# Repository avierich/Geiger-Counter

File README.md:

# Geiger-Counter

A simple geiger counter using a geiger-muller tube.

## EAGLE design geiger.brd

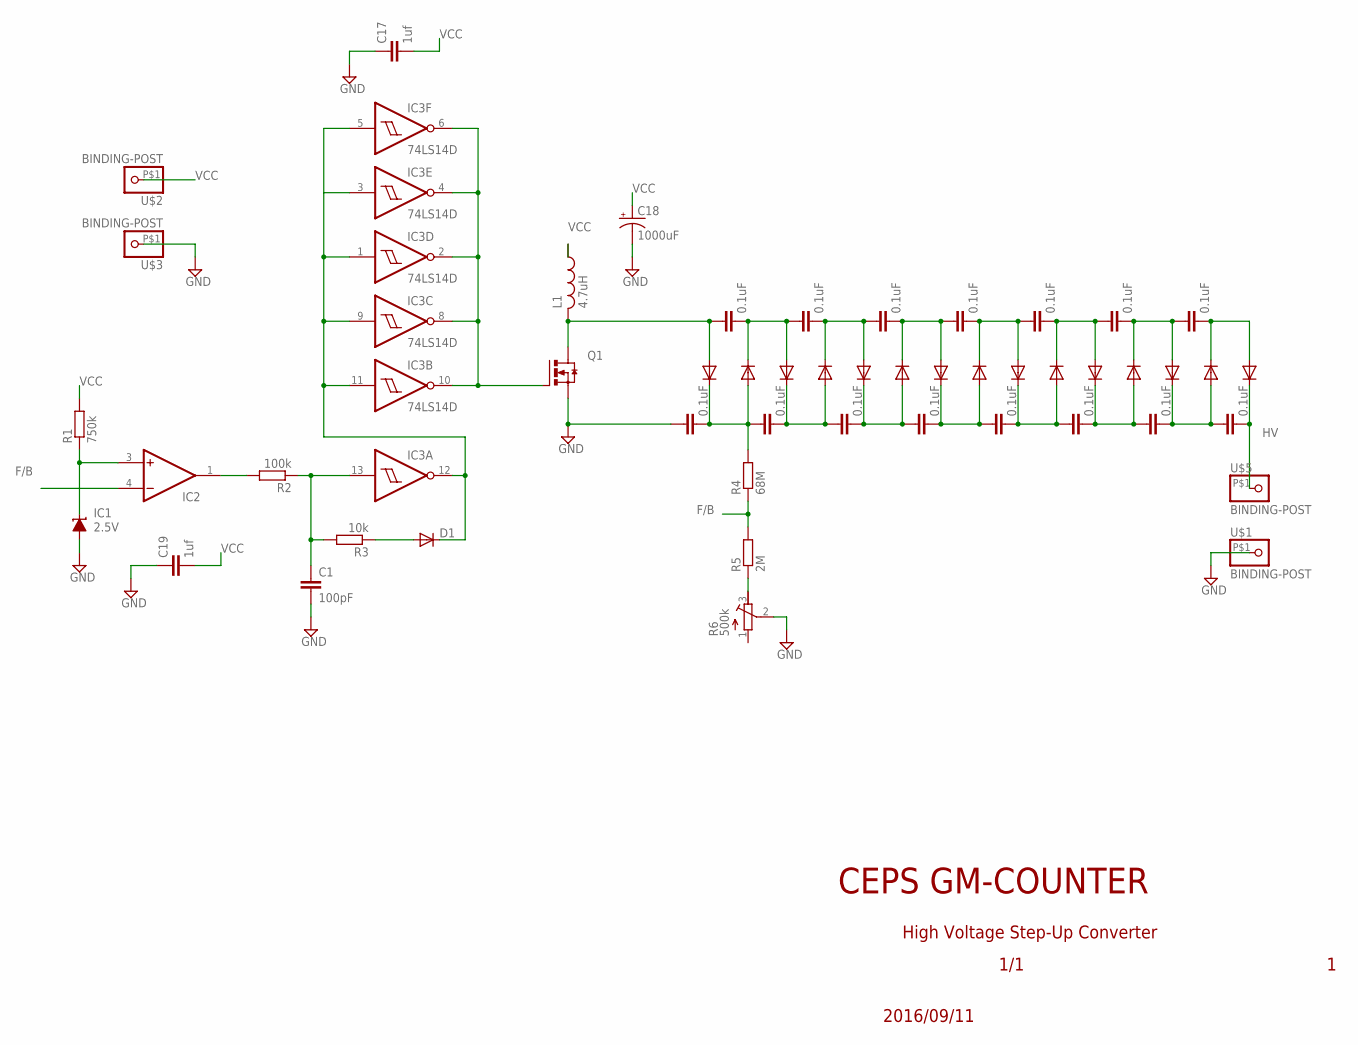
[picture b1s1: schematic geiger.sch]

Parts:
C1: 100pF; C0603
C2, C3, C4, C5, C6, C7, C8, C9, C10, C11, C12, C13, C14, C15, C16: 0.1uF; C0603
C17, C19: 1uf; C0603
C18: 1000uF; TT5D10
D1, D2, D3, D4, D5, D6, D7, D8, D9, D10, D11, D12, D13, D14, D15, D16: 1N4148DO35-7; DO35-7
IC1: 2.5V; DBZ_R-PDSO-G3
IC2: MAX4105EUK; SOT23-5L
IC3: 74LS14D; SO14
L1: 4.7uH; 6000-XXXX-RC
Q1: N-HEXFET-2D_SOT232-IRLL2705; SOT223
R1: 750k; R0603
R2: 100k; R0603
R3: 10k; R0603
R4: 68M; R0603
R5: 2M; R0603
R6: 500k; RTRIM4G/J
U$1, U$2, U$3, U$5: BINDING-POST

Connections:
+HV: C15.2, D15.C, D16.A
F/B: IC2.4 (-IN), R4.1, R5.2
GND: C1.2, C2.1, C17.1, C18.-, C19.1, IC1.2 (A), IC3.7 (GND), Q1.3 (S), R6.2 (S), U$1.P$1, U$3.P$1
HV: C16.2, D16.C, U$5.P$1
unnamed: IC1.1 (C), IC2.3 (+IN), R1.1
unnamed: D1.A, R3.1
unnamed: IC2.1 (OUT), R2.2
unnamed: C1.1, IC3.13 (I), R2.1, R3.2
unnamed: D1.C, IC3.1 (I), IC3.3 (I), IC3.5 (I), IC3.9 (I), IC3.11 (I), IC3.12 (O)
unnamed: IC3.2 (O), IC3.4 (O), IC3.6 (O), IC3.8 (O), IC3.10 (O), Q1.1 (G)
unnamed: C2.2, C4.1, D2.C, D3.A, R4.2
unnamed: C4.2, C6.1, D4.C, D5.A
unnamed: C3.2, C5.1, D3.C, D4.A
unnamed: R5.1, R6.3 (E)
unnamed: C5.2, C7.1, D5.C, D6.A
unnamed: C6.2, C8.1, D6.C, D7.A
unnamed: C7.2, C9.1, D7.C, D8.A
unnamed: C8.2, C10.1, D8.C, D9.A
unnamed: C9.2, C11.1, D9.C, D10.A
unnamed: C11.2, C13.1, D11.C, D12.A
unnamed: C13.2, C15.1, D13.C, D14.A
unnamed: C14.2, C16.1, D14.C, D15.A
unnamed: C12.2, C14.1, D12.C, D13.A
unnamed: C10.2, C12.1, D10.C, D11.A
unnamed: C3.1, D2.A, L1.2, Q1.2 (D), Q1.4 (D)
VCC: C17.2, C18.+, C19.2, IC2.5 (VCC), IC3.14 (VCC), L1.1, R1.2, U$2.P$1
VEE: IC2.2 (VEE)

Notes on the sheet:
High Voltage Step-Up Converter
2016/09/11
1/1
CEPS GM-COUNTER

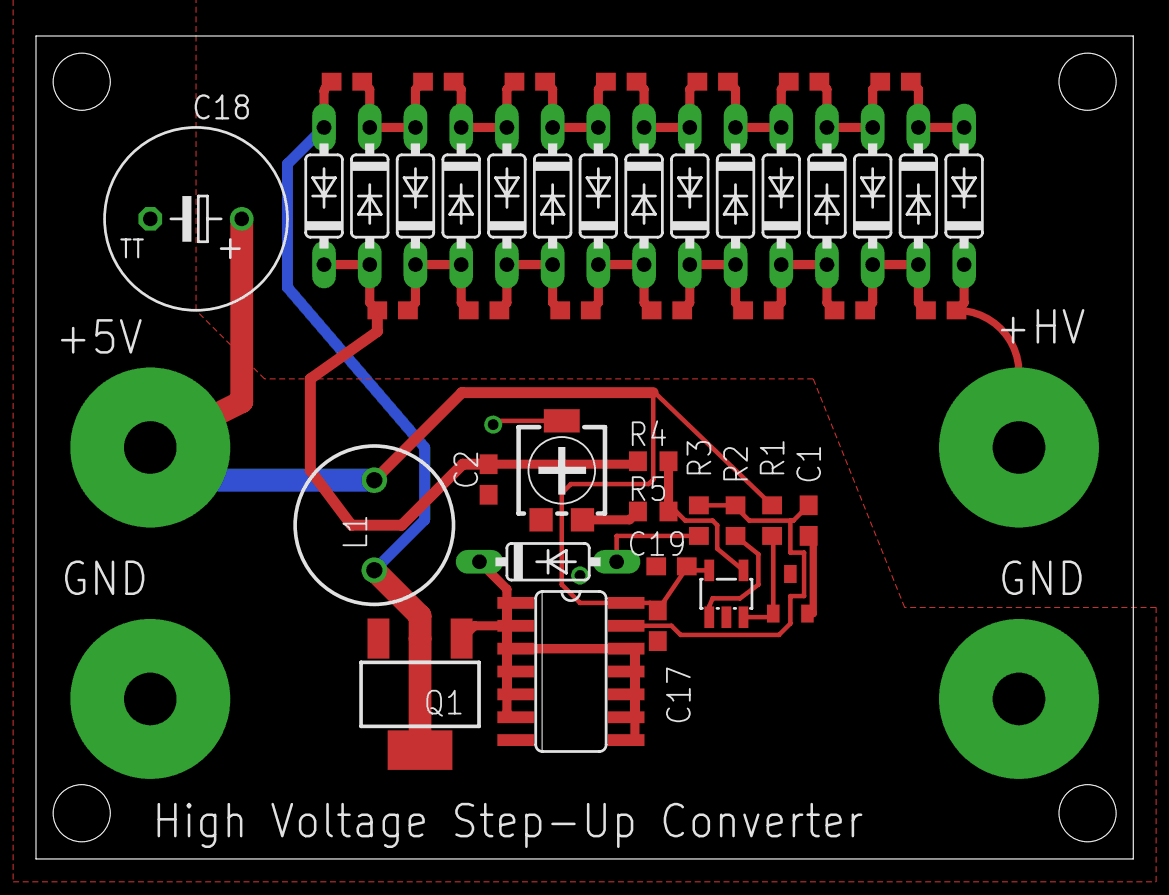
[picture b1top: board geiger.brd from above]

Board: 2 copper layers, 61.0 x 45.7 mm, 50 parts (0 on the bottom side), 26 nets.

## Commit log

2016-06-01 inital commit
2016-06-05 Picking parts
2016-06-06 Completeing power supply on board
2016-09-05 Adding Maxim library and .gitignore
2016-09-06 Created CTC-5 package
2016-09-25 Up to date with built Rev1
